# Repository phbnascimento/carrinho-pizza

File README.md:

# Gigantes de MDF - CARRO-PIZZA! 🚗

## Introdução
Bem-vindo à documentação técnica do projeto de **Carrinho-Pizza**. 
Este firmware foi desenvolvido para a arquitetura AVR (ATmega328P) utilizando manipulação direta de registradores ("Bare Metal") para garantir a máxima eficiência no tempo de resposta dos motores.

### 🎯 Objetivos
* Fazer controle PWM e temporizadores via Timers de Hardware (Timer0 e Timer2).
* Implementar protocolo de comunicação sem fio com o módulo de rádio NRF24L01.
* Demonstrar conhecimentos no desenvolvimento com microcontroladores.

---

## 🛠️ Hardware Utilizado

| Componente | Especificação | Função |
| :--- | :--- | :--- |
| **MCU** | ATmega328P (16MHz) | "Cérebro" do sistema |
| **Rádio** | NRF24L01+ | Comunicação 2.4GHz |
| **Driver** | Ponte H (L298N) | Controle de potência dos motores |
| **Sensores** |  LDR | Detecção de luz do ambiente |

---

## 🔌 Pinagem (Pinout)

Abaixo está o mapeamento físico dos pinos do microcontrolador para os periféricos:

* **Motores:**
    * `PD6 (OC0A)`: PWM Motor Esquerdo
    * `PD3 (OC2B)`: PWM Motor Direito
    * `PD1/PD2/PD4/PD5`: Controle de Direção (Ponte H)
* **Comunicação:**
    * `PB1/PB2`: Controle do Rádio (CE/CSN)
    * `SPI`: Padrão do ATmega
* **Interface:**
    * `PD7`: Botão para debug (Pull-up)
    * `PC1-PC3`: LEDs de "Vida" do carrinho

---

## 🚀 Como Compilar

1.  Abra o arquivo `Makefile`.
1.  Configure o `PORT` para a porta USB correta onde será feita a transmissão do código.
2.  Compile apenas utilizando o comando `make DIR=<carrinho/controle>`.

> **Nota:** Certifique-se de que a biblioteca `nrf24_avr.h` esteja presente nos dois diretórios.

---

**Autores:** Bruno Garcia Carvalho, Pedro Henrique Brito, Pedro Henrique Cretella  
**Disciplina:** Programação de Hardware / Microcontroladores  
**Data:** Novembro 2025

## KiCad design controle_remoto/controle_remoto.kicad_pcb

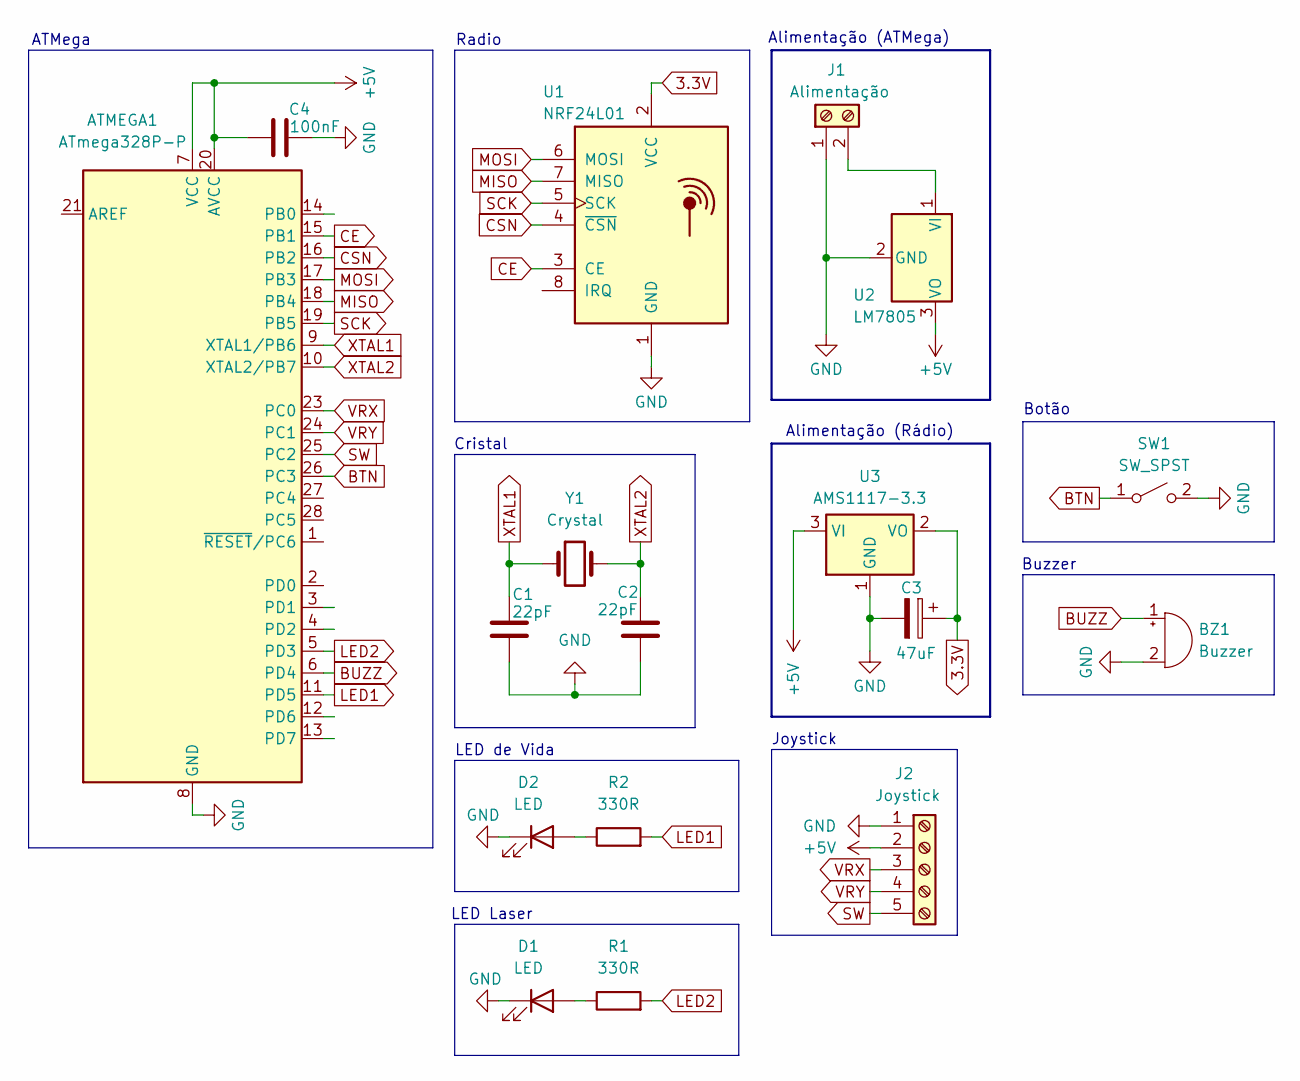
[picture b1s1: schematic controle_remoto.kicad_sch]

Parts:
ATMEGA1: ATmega328P-P; DIP-28_W7.62mm_LongPads
BZ1: Buzzer; Buzzer_12x9.5RM7.6
C1, C2: 22pF; C_Disc_D3.4mm_W2.1mm_P2.50mm
C3: 47uF; CP_Radial_D8.0mm_P3.50mm
C4: 100nF; C_Rect_L13.0mm_W4.0mm_P10.00mm_FKS3_FKP3_MKS4
D1, D2: LED; TerminalBlock_MaiXu_MX126-5.0-02P_1x02_P5.00mm
J1: Alimentação; TerminalBlock_MaiXu_MX126-5.0-02P_1x02_P5.00mm
J2: Joystick; TerminalBlock_MaiXu_MX126-5.0-05P_1x05_P5.00mm
R1, R2: 330R; R_Axial_DIN0207_L6.3mm_D2.5mm_P10.16mm_Horizontal
SW1: SW_SPST; TerminalBlock_MaiXu_MX126-5.0-02P_1x02_P5.00mm
U1: NRF24L01; nRF24L01_Breakout
U2: LM7805; TO-220-3_Vertical
U3: AMS1117-3.3; SOT-223-3_TabPin2
Y1: Crystal; Crystal_HC49-4H_Vertical

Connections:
3.3V: C3.1, U1.2 (VCC), U3.2 (VO)
+5V: ATMEGA1.7 (VCC), ATMEGA1.20 (AVCC), C4.1, J2.2, U2.3 (VO), U3.3 (VI)
BTN: ATMEGA1.26 (PC3), SW1.1 (A)
BUZZ: ATMEGA1.6 (PD4), BZ1.1 (+)
CE: ATMEGA1.15 (PB1), U1.3 (CE)
CSN: ATMEGA1.16 (PB2), U1.4 (~CSN)
GND: ATMEGA1.8 (GND), ATMEGA1.22 (GND), BZ1.2 (-), C1.2, C2.2, C3.2, C4.2, D1.1 (K), D2.1 (K), J1.1, J2.1, SW1.2 (B), U1.1 (GND), U2.2 (GND), U3.1 (GND)
LED1: ATMEGA1.11 (PD5), R2.2
LED2: ATMEGA1.5 (PD3), R1.2
MISO: ATMEGA1.18 (PB4), U1.7 (MISO)
MOSI: ATMEGA1.17 (PB3), U1.6 (MOSI)
unnamed: D1.2 (A), R1.1
unnamed: D2.2 (A), R2.1
unnamed: J1.2, U2.1 (VI)
SCK: ATMEGA1.19 (PB5), U1.5 (SCK)
SW: ATMEGA1.25 (PC2), J2.5
VRX: ATMEGA1.23 (PC0), J2.3
VRY: ATMEGA1.24 (PC1), J2.4
XTAL1: ATMEGA1.9 (XTAL1/PB6), C1.1, Y1.1
XTAL2: ATMEGA1.10 (XTAL2/PB7), C2.1, Y1.2

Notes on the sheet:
LED Laser
Cristal
Buzzer
ATMega
LED de Vida
Alimentação (ATMega)
Joystick
Radio
Alimentação (Rádio)
Botão

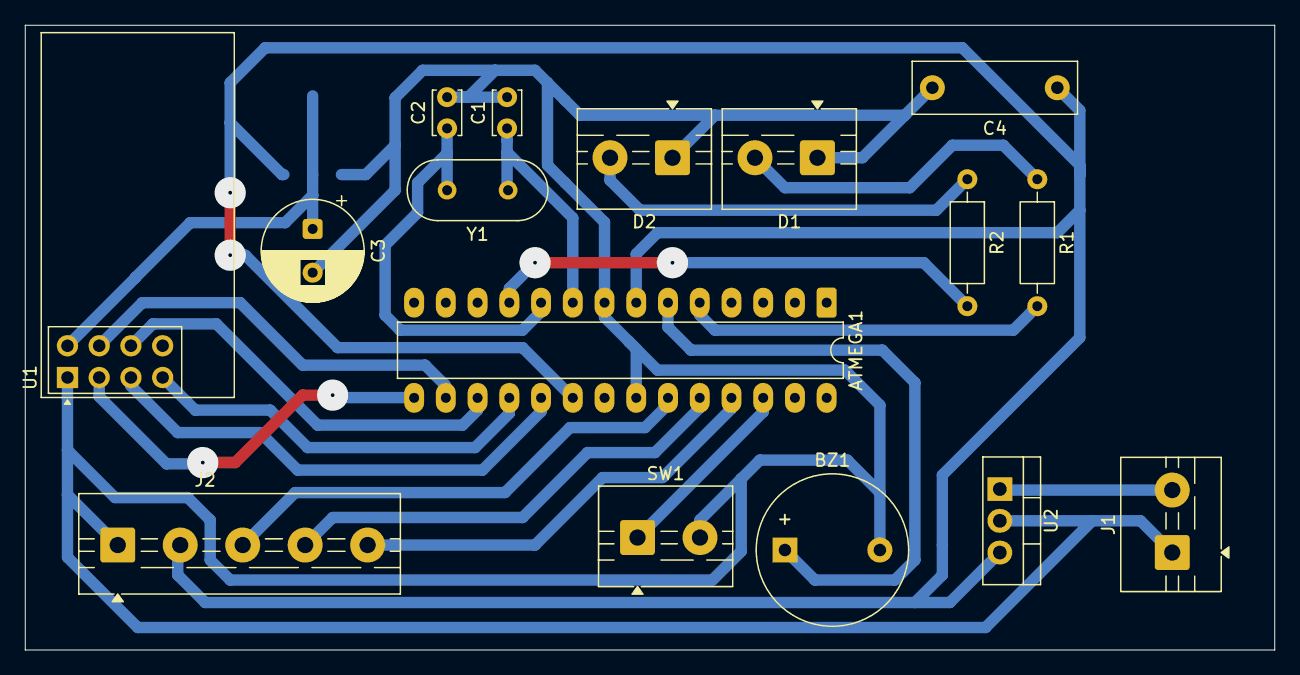
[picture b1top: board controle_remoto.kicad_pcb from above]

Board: 2 copper layers, 100.0 x 50.0 mm, 17 parts (1 on the bottom side), 20 nets.

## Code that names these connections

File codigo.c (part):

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#define LED(LEDNUM, STATE) (STATE ? (PORTC |=  (1 << (LEDNUM))) : (PORTC &= ~(1 << (LEDNUM))))

/** @def LED1
 * @brief Pino do LED indicativo 1 (PC1 / A1). */
#define LED1 1

/** @def LED2
 * @brief Pino do LED indicativo 2 (PC2 / A2). */
#define LED2 2

/** @def LED3
 * @brief Pino do LED indicativo 3 (PC3 / A3). */
#define LED3 3

/* --- Pinos da Ponte H (Motor Driver) --- */
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 * @brief Controle de direção Motor A (PD2). */
#define IN1 2
/** @def ENB
 * @brief Enable/PWM do Motor B (PD3 - OC2B). */
#define ENB 3
/** @def IN4
 * @brief Controle de direção Motor B (PD4). */
#define IN4 4
/** @def IN3
 * @brief Controle de direção Motor B (PD5). */
#define IN3 5
/** @def ENA
 * @brief Enable/PWM do Motor A (PD6 - OC0A). */
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
/** @def BTN
 * @brief Pino do Botão de usuário (PD7). */
#define BTN 7

/** @def LASER
 * @brief Pino de controle do Laser (PB0). */
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 * Configurações detalhadas:
 * - **ADC**: Referência AVCC, Prescaler 128 (para clock de 16MHz).
 * - **Timer0 (PD6)**: Fast PWM, Non-Inverting, Prescaler 8.
 * - **Timer2 (PD3)**: Fast PWM, Non-Inverting, Prescaler 8.
 */
void analog_setup(void) {
  // Setando para leitura nas portas analógicas (ADC)
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  TCCR0A = (1<<WGM00) | (1<<WGM01) | (1<<COM0A1);
  TCCR0B = (1<<CS01);  // CS01: Prescaler 8 (frequência do PWM adequada p/ motores)

  // Setup PWM PD3 (Timer2 - 8 bits)
  DDRD |= (1 << PD3); // Configura PD3 como saída
  // WGM20/21: Fast PWM mode | COM2B1: PWM no pino OC2B (PD3)
  TCCR2A = (1<<WGM20) | (1<<WGM21) | (1<<COM2B1);
  TCCR2B = (1<<CS21); // CS21: Prescaler 8
}
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 */
void analog_write(uint8_t pin, uint8_t value) {
    if (pin == 6)      OCR0A = value;  // Timer0 A (PD6)
    else if (pin == 3) OCR2B = value;  // Timer2 B (PD3)
}

/**
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 *
 * Configurações de Hardware:
 * - DDRB: PB0 como Saída.
 * - DDRC: PC1, PC2, PC3 como Saída (LEDs).
 * - DDRD: Pinos da Ponte H como Saída, Botão como Entrada.
 * - Pull-up ativado no pino do botão.
 * - Inicialização do Rádio NRF24L01.
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int main() {
  // Configuração de Direção dos Pinos (Data Direction Register)
  DDRB |= 0b00000001; // PB0 Output (Laser)
  DDRC |= 0b00001110; // PC1-PC3 Output (LEDs)
  DDRD |= 0b01111110; // PD1-PD6 Output (Motores), PD7 Input

  // Ativa resistor de Pull-up interno no pino PD7 (Botão)
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  analog_setup();

  // Configuração do Rádio NRF24
  // CE no pino 9 (PB1), CSN no pino 10 (PB2)
  nrf24_begin(9, 10, RF24_SPI_SPEED);
  nrf24_openReadingPipe(0, addr);
  nrf24_setChannel(76); // Canal RF 76
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
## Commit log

2025-11-29 primeiro commit
2025-11-29 gitignore
2025-11-29 removendo arquivos gerados
2025-11-29 doxygen
2025-11-29 README.md atualizado
2025-11-29 custom.css
2025-11-29 atualizações no código
2025-11-29 mudanças
2025-11-29 código ino
2025-11-29 doxygen ino
2025-11-29 correção
2025-11-29 projetos KiCad (esquemático e PCB)
2025-11-29 motor_setup
2025-11-29 sistema de vida
2025-11-30 retoques no código c
2025-11-30 finalização do controle em c
2025-11-30 documentação finalizada
2025-12-12 implementando timers
2025-12-12 sistema gameover
2025-12-13 ajustes finais
2025-12-13 doxygen atualizado
